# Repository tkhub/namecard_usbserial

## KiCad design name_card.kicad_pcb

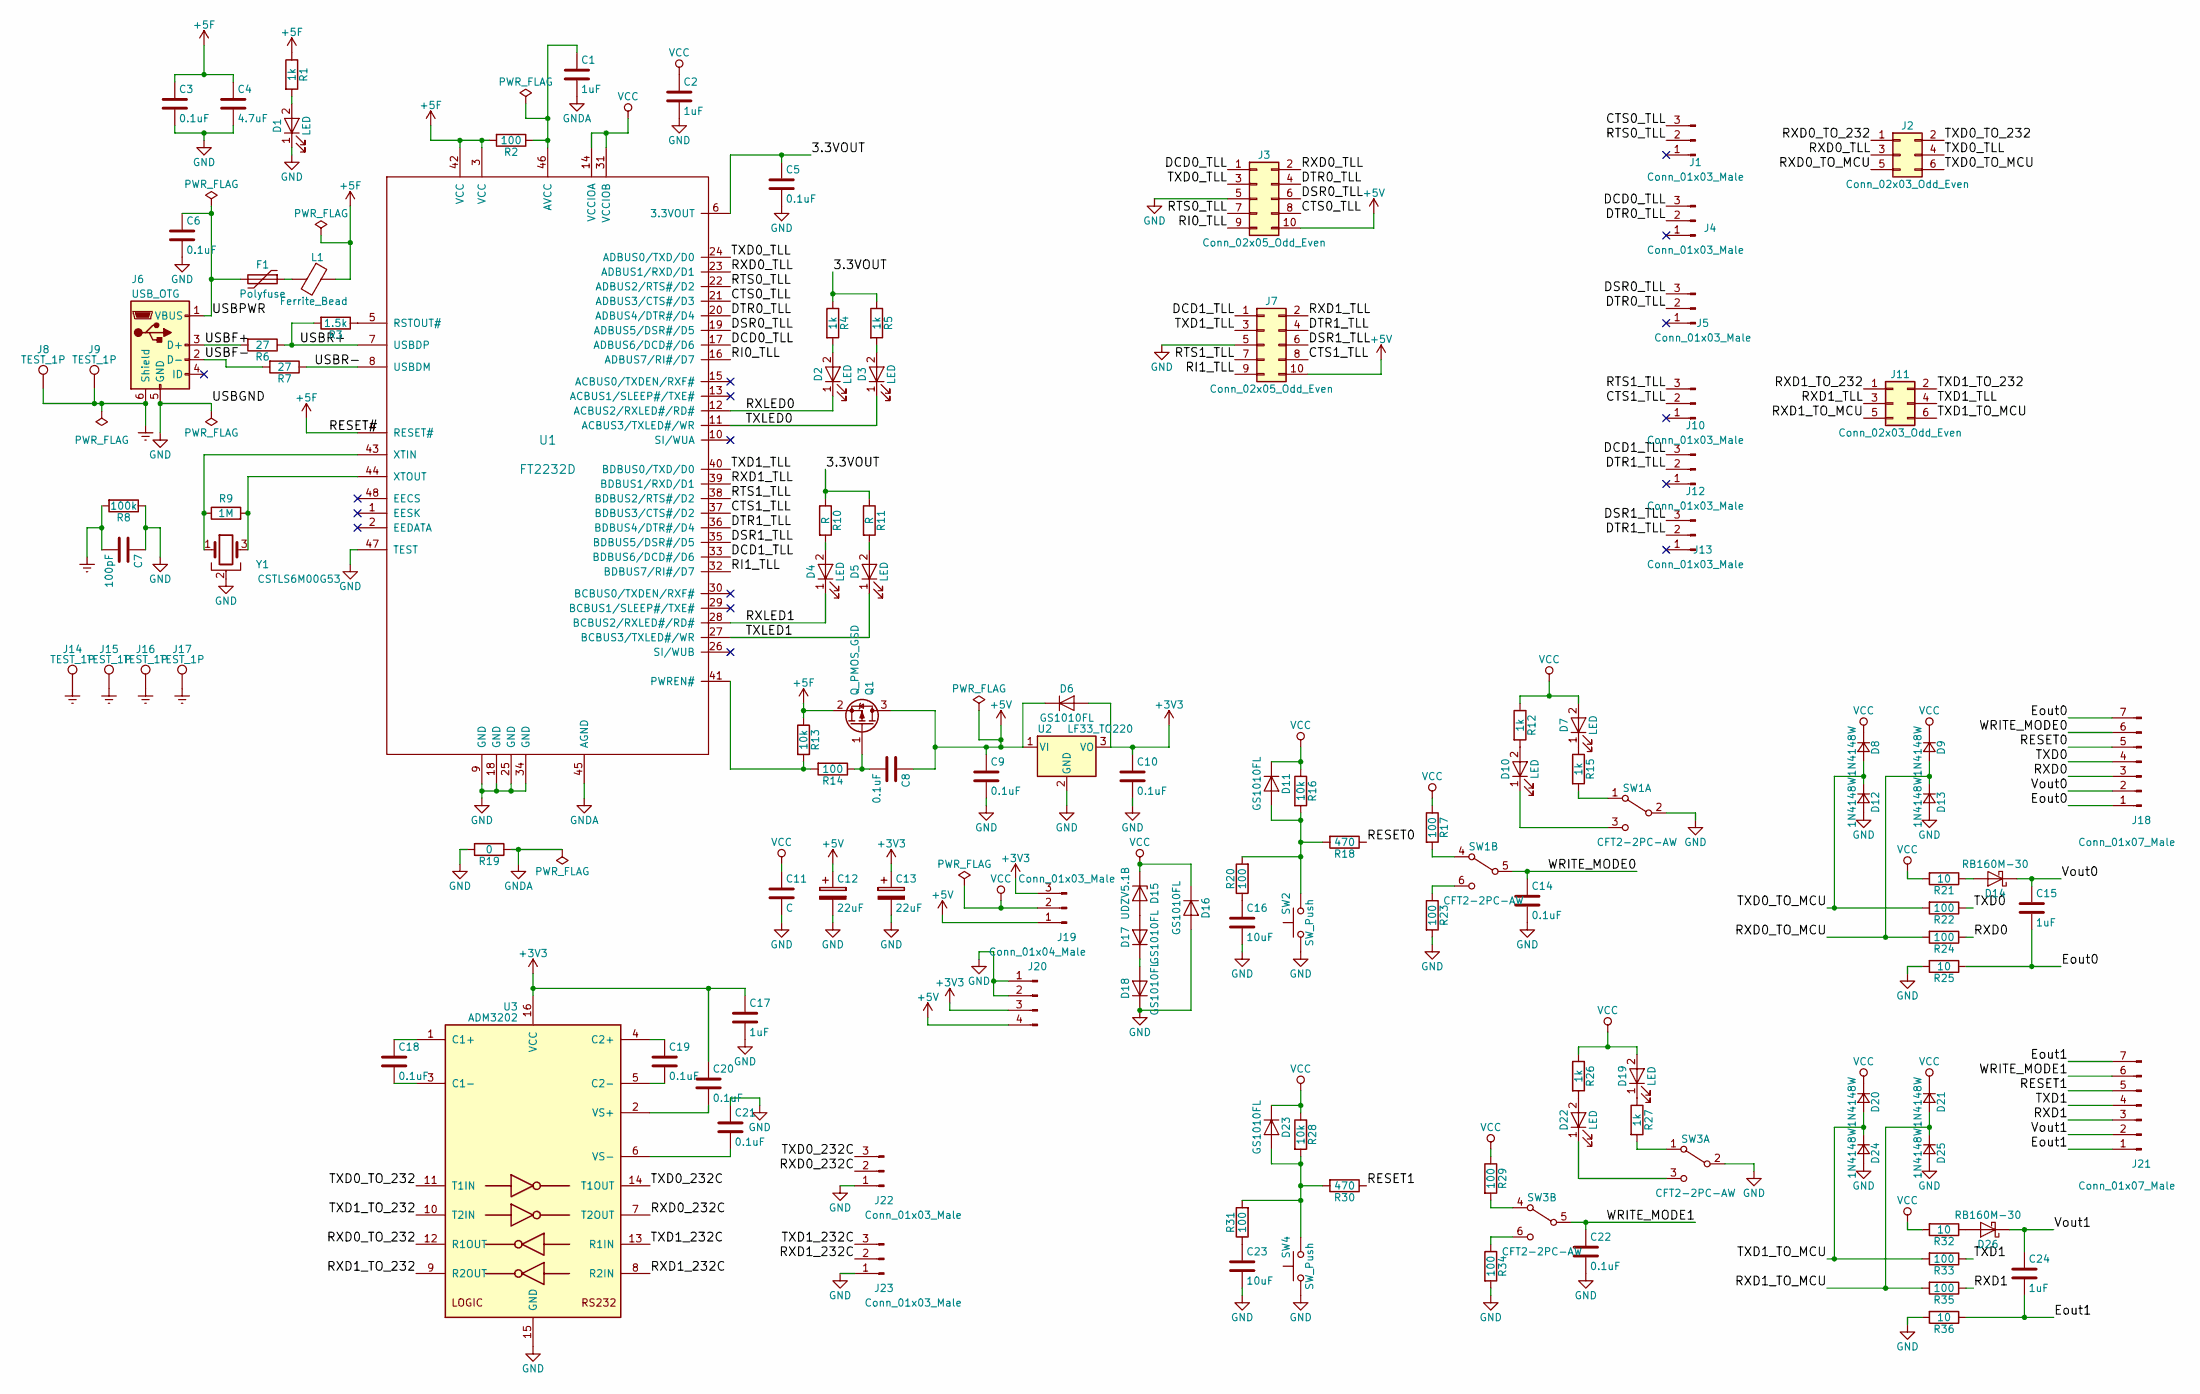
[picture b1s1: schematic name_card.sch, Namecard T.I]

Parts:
C1, C2, C15, C17, C24: 1uF; C_0603_HandSoldering
C3, C5, C6, C8, C9, C10, C14, C18, C19, C20, C21, C22: 0.1uF; C_0603_HandSoldering
C4: 4.7uF; C_1206_HandSoldering
C7: 100pF; C_0603_HandSoldering
C11: C; C_0805_HandSoldering
C12, C13: 22uF; CP_Tantalum_Case-B_EIA-3528-21_Hand
C16, C23: 10uF; C_1210_HandSoldering
D1, D2, D3, D4, D5, D7, D10, D19, D22: LED; LED_0603_HandSoldering
D6, D11, D16, D17, D18, D23: GS1010FL; D_SOD-123F
D8, D9, D12, D13, D20, D21, D24, D25: 1N4148W; D_SOD-123F
D14, D26: RB160M-30; D_SOD-123F
D15: UDZV5.1B; D_SOD-323
F1: Polyfuse; R_Axial_DIN0207_L6.3mm_D2.5mm_P5.08mm_Vertical
J1, J4, J5, J10, J12, J13: Conn_01x03_Male; Pin_Header_Straight_1x03_Pitch1.27mm
J2, J11: Conn_02x03_Odd_Even; Pin_Header_Straight_2x03_Pitch1.27mm
J3, J7: Conn_02x05_Odd_Even; Pin_Header_Straight_2x05_Pitch2.54mm_SMD
J6: USB_OTG; USB_Micro-B
J8, J9: TEST_1P; SolderWirePad_2x_0-8mmDrill
J14, J15, J16, J17: TEST_1P; MountingHole_2.2mm_M2_Pad
J18, J21: Conn_01x07_Male; Pin_Header_Straight_1x07_Pitch2.54mm
J19, J22, J23: Conn_01x03_Male; Pin_Header_Straight_1x03_Pitch2.54mm
J20: Conn_01x04_Male; Pin_Header_Straight_1x04_Pitch2.54mm
L1: Ferrite_Bead; R_0805_HandSoldering
Q1: Q_PMOS_GSD; SOT-23
R1, R4, R5, R12, R15, R26, R27: 1k; R_0603_HandSoldering
R2, R14, R17, R20, R22, R23, R24, R29, R31, R33, R34, R35: 100; R_0603_HandSoldering
R3: 1.5k; R_0603_HandSoldering
R6, R7: 27; R_0603_HandSoldering
R8: 100k; R_0603_HandSoldering
R9: 1M; R_0603_HandSoldering
R10, R11: R; R_0603_HandSoldering
R13, R16, R28: 10k; R_0603_HandSoldering
R18, R30: 470; R_0603_HandSoldering
R19: 0; R_0402_NoSilk
R21, R25, R32, R36: 10; R_0603_HandSoldering
SW1, SW3: CFT2-2PC-AW; SW_CuK_JS202011CQN_DPDT_Straight
SW2, SW4: SW_Push; SW_PUSH_6mm
U1: FT2232D; LQFP-48_7x7mm_Pitch0.5mm
U2: LF33_TO220; TO-251_IPAK_Vertical
U3: ADM3202; SOP-16_4.4x10.4mm_Pitch1.27mm
Y1: CSTLS6M00G53; Crystal_HC52-U-3pin_Vertical

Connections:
+3V3: C10.1, C13.1, C17.1, C20.1, D6.2 (A), J19.3, J20.3, U2.3 (VO), U3.16 (VCC)
+5F: C3.1, C4.1, L1.1, Q1.2 (S), R1.1, R2.2, R13.1, U1.3 (VCC), U1.4 (RESET#), U1.42 (VCC)
+5V: C8.1, C9.1, C12.1, D6.1 (K), J3.10, J7.10, J19.1, J20.4, Q1.3 (D), U2.1 (VI)
/3.3VOUT: C5.1, R4.1, R5.1, R10.1, R11.1, U1.6 (3.3VOUT)
/CTS0_TLL: J1.3, J3.8, U1.21 (ADBUS3/CTS#/D3)
/CTS1_TLL: J7.8, J10.2, U1.37 (BDBUS3/CTS#/D2)
/DCD0_TLL: J3.1, J4.3, U1.17 (ADBUS6/DCD#/D6)
/DCD1_TLL: J7.1, J12.3, U1.33 (BDBUS6/DCD#/D6)
/DSR0_TLL: J3.6, J5.3, U1.19 (ADBUS5/DSR#/D5)
/DSR1_TLL: J7.6, J13.3, U1.35 (BDBUS5/DSR#/D5)
/DTR0_TLL: J3.4, J4.2, J5.2, U1.20 (ADBUS4/DTR#/D4)
/DTR1_TLL: J7.4, J12.2, J13.2, U1.36 (BDBUS4/DTR#/D4)
/Eout0: C15.2, J18.1, J18.7, R25.1
/Eout1: C24.2, J21.1, J21.7, R36.1
/RESET0: J18.5, R18.1
/RESET1: J21.5, R30.1
/RI0_TLL: J3.9, U1.16 (ADBUS7/RI#/D7)
/RI1_TLL: J7.9, U1.32 (BDBUS7/RI#/D7)
/RTS0_TLL: J1.2, J3.7, U1.22 (ADBUS2/RTS#/D2)
/RTS1_TLL: J7.7, J10.3, U1.38 (BDBUS2/RTS#/D2)
/RXD0: J18.3, R24.1
/RXD0_232C: J22.2, U3.7 (T2OUT)
/RXD0_TLL: J2.3, J3.2, U1.23 (ADBUS1/RXD/D1)
/RXD0_TO_232: J2.1, U3.12 (R1OUT)
/RXD0_TO_MCU: D9.2 (A), D13.1 (K), J2.5, R24.2
/RXD1: J21.3, R35.1
/RXD1_232C: J23.2, U3.8 (R2IN)
/RXD1_TLL: J7.2, J11.3, U1.39 (BDBUS1/RXD/D1)
/RXD1_TO_232: J11.1, U3.9 (R2OUT)
/RXD1_TO_MCU: D21.2 (A), D25.1 (K), J11.5, R35.2
/RXLED0: D2.1 (K), U1.12 (ACBUS2/RXLED#/RD#)
/RXLED1: D4.1 (K), U1.28 (BCBUS2/RXLED#/RD#)
/TXD0: J18.4, R22.1
/TXD0_232C: J22.3, U3.14 (T1OUT)
/TXD0_TLL: J2.4, J3.3, U1.24 (ADBUS0/TXD/D0)
/TXD0_TO_232: J2.2, U3.11 (T1IN)
/TXD0_TO_MCU: D8.2 (A), D12.1 (K), J2.6, R22.2
/TXD1: J21.4, R33.1
/TXD1_232C: J23.3, U3.13 (R1IN)
/TXD1_TLL: J7.3, J11.4, U1.40 (BDBUS0/TXD/D0)
/TXD1_TO_232: J11.2, U3.10 (T2IN)
/TXD1_TO_MCU: D20.2 (A), D24.1 (K), J11.6, R33.2
/TXLED0: D3.1 (K), U1.11 (ACBUS3/TXLED#/WR)
/TXLED1: D5.1 (K), U1.27 (BCBUS3/TXLED#/WR)
/USBF+: J6.3 (D+), R6.2
/USBF-: J6.2 (D-), R7.2
/USBPWR: C6.1, F1.2, J6.1 (VBUS)
/USBR+: R3.2, R6.1, U1.7 (USBDP)
/USBR-: R7.1, U1.8 (USBDM)
/Vout0: C15.1, D14.1 (K), J18.2
/Vout1: C24.1, D26.1 (K), J21.2
/WRITE_MODE0: C14.1, J18.6, SW1.5 (B)
/WRITE_MODE1: C22.1, J21.6, SW3.5 (B)
Earth: C7.2, J6.6 (Shield), J8.1, J9.1, J14.1, J15.1, J16.1, J17.1, R8.2
GND: C2.2, C3.2, C4.2, C5.2, C6.2, C7.1, C9.2, C10.2, C11.2, C12.2, C13.2, C14.2, C16.2, C17.2, C21.1, C22.2, C23.2, D1.1 (K), D12.2 (A), D13.2 (A), D16.2 (A), D18.1 (K), D24.2 (A), D25.2 (A), J3.5, J6.5 (GND), J7.5, J20.1, J20.2, J22.1, J23.1, R8.1, R19.2, R23.2, R25.2, R34.2, R36.2, SW1.2 (B), SW2.1, SW3.2 (B), SW4.1, U1.9 (GND), U1.18 (GND), U1.25 (GND), U1.34 (GND), U1.47 (TEST), U2.2 (GND), U3.15 (GND), Y1.2
GNDA: C1.2, R19.1, U1.45 (AGND)
unnamed: C1.1, R2.1, U1.46 (AVCC)
unnamed: C8.2, Q1.1 (G), R14.1
unnamed: C16.1, R20.1
unnamed: C18.1, U3.1 (C1+)
unnamed: C18.2, U3.3 (C1-)
unnamed: C19.1, U3.4 (C2+)
unnamed: C19.2, U3.5 (C2-)
unnamed: C20.2, U3.2 (VS+)
unnamed: C21.2, U3.6 (VS-)
unnamed: C23.1, R31.1
unnamed: D1.2 (A), R1.2
unnamed: D2.2 (A), R4.2
unnamed: D3.2 (A), R5.2
unnamed: D4.2 (A), R10.2
unnamed: D5.2 (A), R11.2
unnamed: D7.1 (K), R15.1
unnamed: D10.1 (K), SW1.3 (C)
unnamed: D10.2 (A), R12.2
unnamed: D11.2 (A), R16.2, R18.2, R20.2, SW2.2
unnamed: D14.2 (A), R21.1
unnamed: D15.2 (A), D17.2 (A)
unnamed: D17.1 (K), D18.2 (A)
unnamed: D19.1 (K), R27.1
unnamed: D22.1 (K), SW3.3 (C)
unnamed: D22.2 (A), R26.2
unnamed: D23.2 (A), R28.2, R30.2, R31.2, SW4.2
unnamed: D26.2 (A), R32.1
unnamed: F1.1, L1.2
unnamed: R3.1, U1.5 (RSTOUT#)
unnamed: R9.1, U1.43 (XTIN), Y1.1
unnamed: R9.2, U1.44 (XTOUT), Y1.3
unnamed: R13.2, R14.2, U1.41 (PWREN#)
unnamed: R15.2, SW1.1 (A)
unnamed: R17.2, SW1.4 (A)
unnamed: R23.1, SW1.6 (C)
unnamed: R27.2, SW3.1 (A)
unnamed: R29.2, SW3.4 (A)
unnamed: R34.1, SW3.6 (C)
VCC: C2.1, C11.1, D7.2 (A), D8.1 (K), D9.1 (K), D11.1 (K), D15.1 (K), D16.1 (K), D19.2 (A), D20.1 (K), D21.1 (K), D23.1 (K), J19.2, R12.1, R16.1, R17.1, R21.2, R26.1, R28.1, R29.1, R32.2, U1.14 (VCCIOA), U1.31 (VCCIOB)

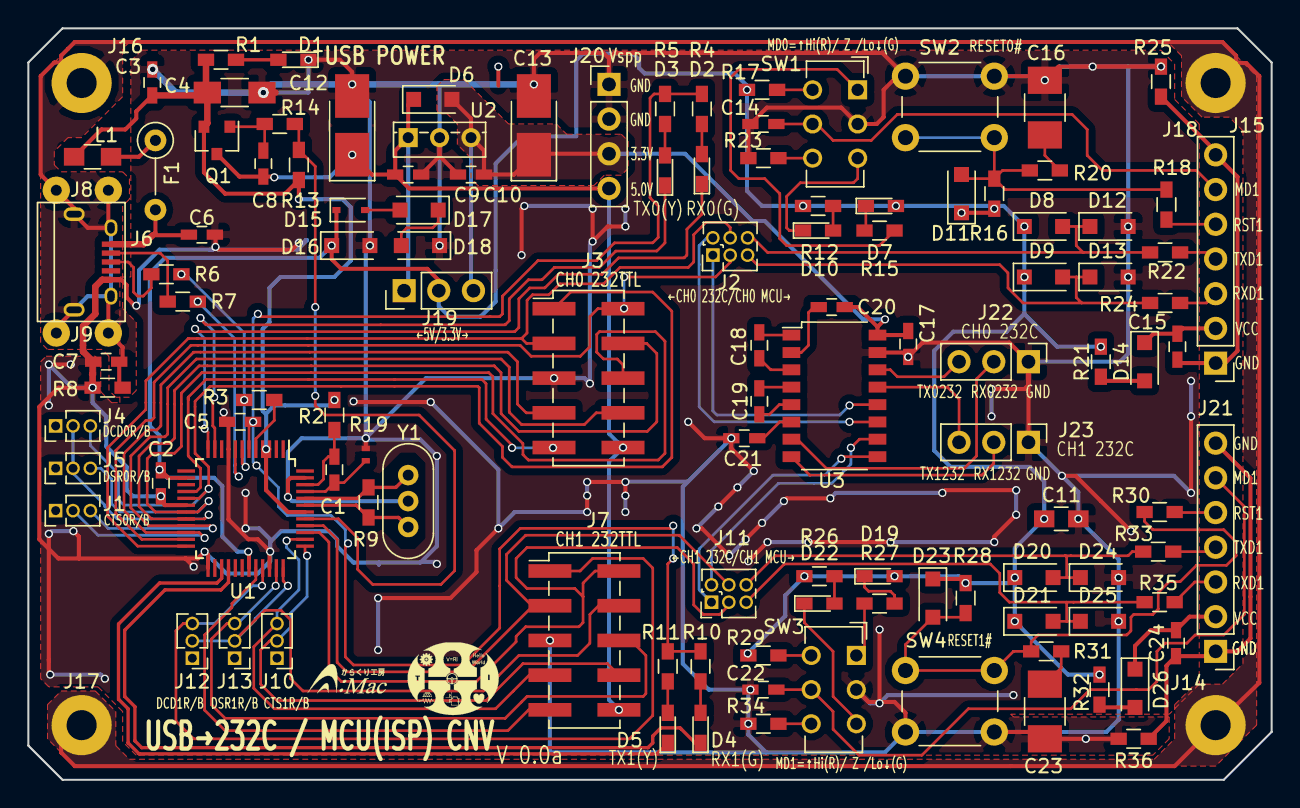
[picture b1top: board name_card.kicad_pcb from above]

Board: 2 copper layers, 91.0 x 55.0 mm, 120 parts (0 on the bottom side), 95 nets.

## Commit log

2019-01-08 Add files via upload
    FirstCommit
